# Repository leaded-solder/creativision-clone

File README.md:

# Introduction
TODO

# Current Status

After bodging, version 0.1 of the Derivavision runs a game of _Sonic Invaders_, but a controller interface has not yet been developed. No other cartridges have been tested.

# Thank You
 - [Creativision Datasette Interface](http://www.8bit-homecomputermuseum.at/repair/creativision_datasette_interface/Creativision_datasette_interface.html) for clearing up the mystery of J3
 - Scouter3d for [keyboard and joystick mappings](http://www.madrigaldesign.it/forum/viewtopic.php?t=354)

# Other Libraries
 - [6502-kicad-library](https://github.com/Alarm-Siren/6502-kicad-library): 6502A CPU symbol
 - [CreativisionMegaCartV2](https://github.com/cheshirenoir/CreativisionMegaCartV2) for help with the cartridge edge

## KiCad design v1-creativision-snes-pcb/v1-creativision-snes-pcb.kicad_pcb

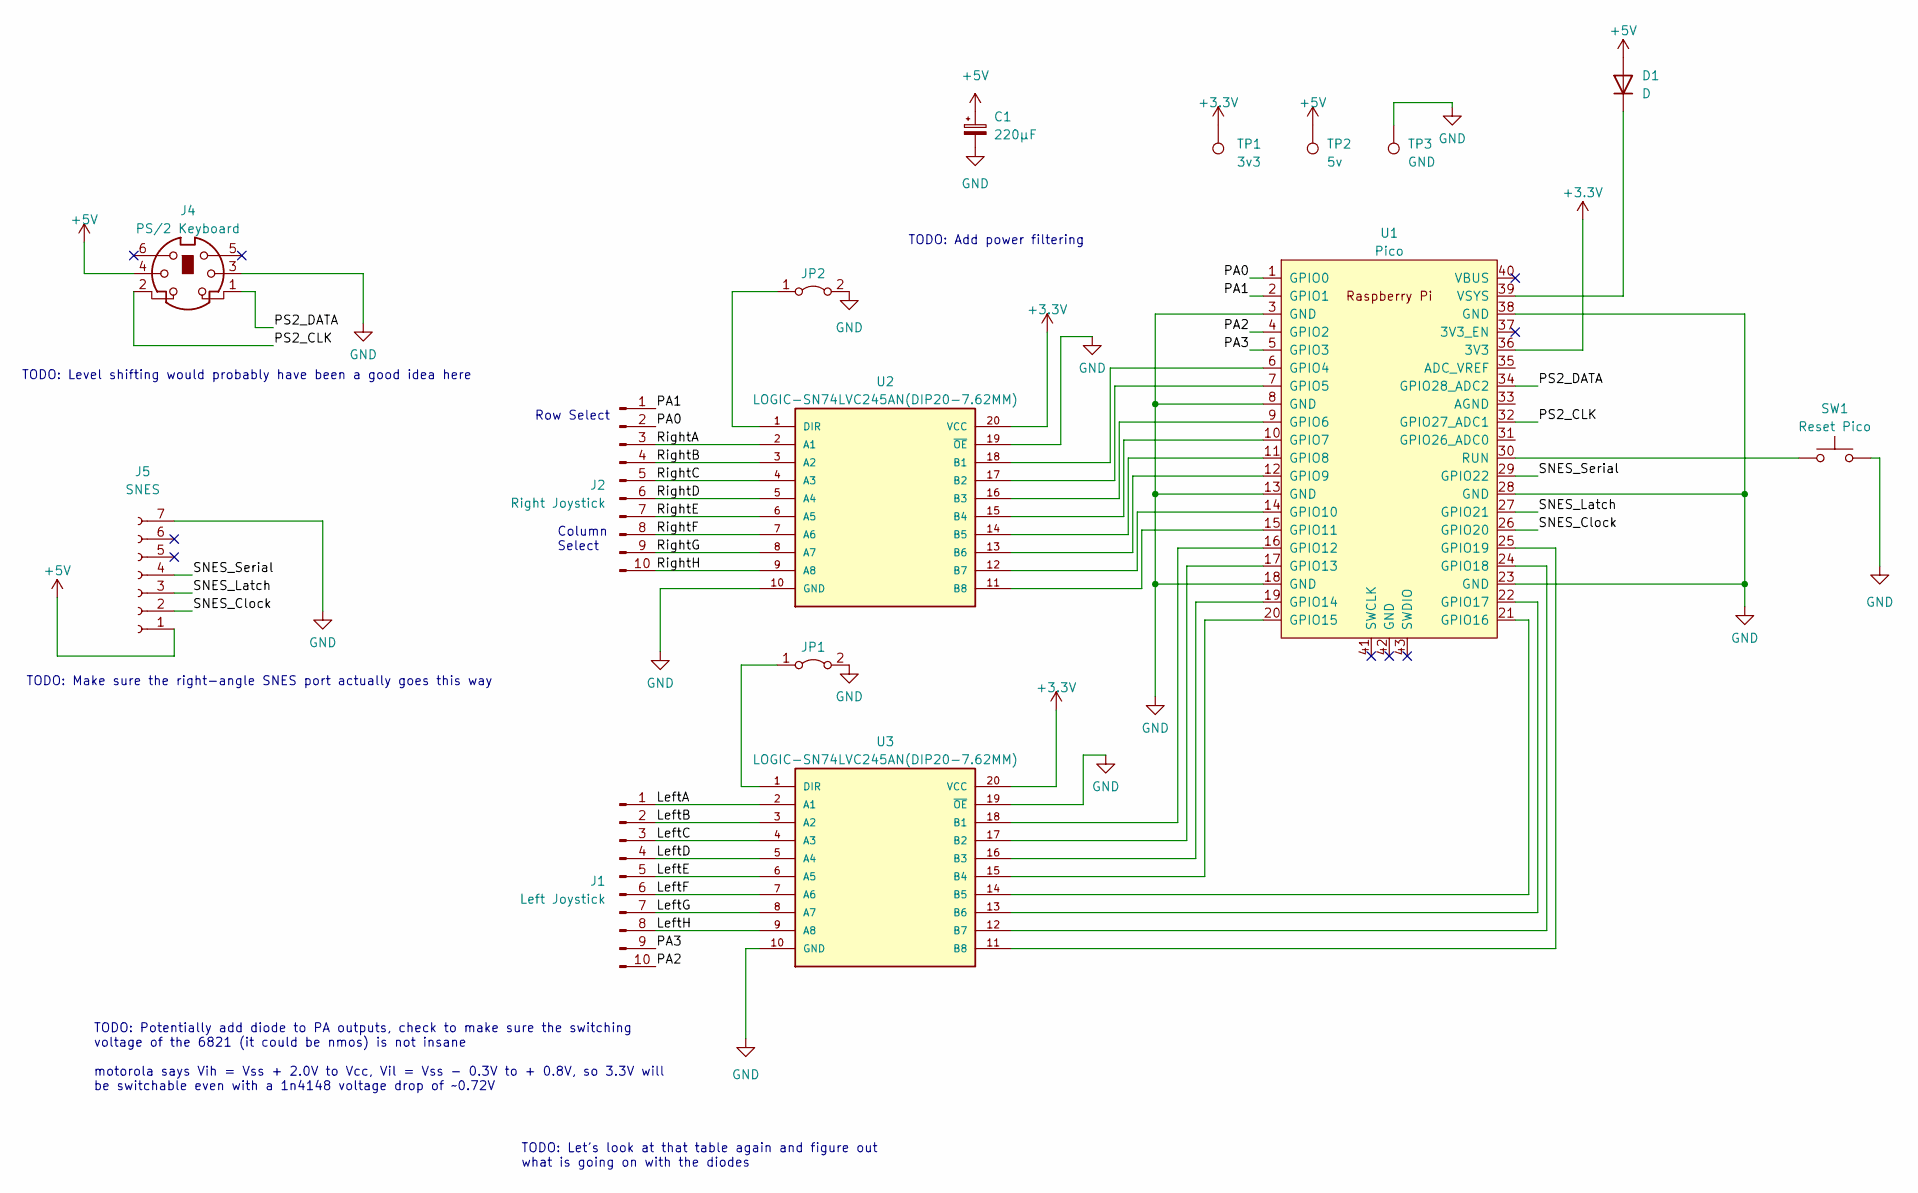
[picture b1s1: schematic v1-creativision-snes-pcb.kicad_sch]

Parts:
C1: 220µF; CP_Radial_D6.3mm_P2.50mm
D1: D; D_DO-15_P10.16mm_Horizontal
J1: Left Joystick; PinHeader_1x10_P2.54mm_Horizontal
J2: Right Joystick; PinHeader_1x10_P2.54mm_Horizontal
J4: PS/2 Keyboard; CUI_MD-60FC
J5: SNES; GAMING_SNES
JP1, JP2: Jumper_2_Bridged; SolderJumper-2_P1.3mm_Bridged2Bar_Pad1.0x1.5mm
SW1: Reset Pico; SW_PUSH_6mm
TP1: 3v3; TestPoint_Loop_D1.80mm_Drill1.0mm_Beaded
TP2: 5v; TestPoint_Loop_D1.80mm_Drill1.0mm_Beaded
TP3: GND; TestPoint_Loop_D1.80mm_Drill1.0mm_Beaded
U1: Pico; RPi_Pico_SMD_TH
U2, U3: LOGIC-SN74LVC245AN(DIP20-7.62MM); DIP-20_W7.62mm_Socket_LongPads; MPN SN74LVC245AN; DigiKey_Part_Number 2156-SN74LVC245AN-ND

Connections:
+3.3V: TP1.1, U1.36 (3V3), U2.20 (VCC), U3.20 (VCC)
+5V: C1.1, D1.2 (A), J4.4, J5.1, TP2.1
/LeftA: J1.1, U3.2 (A1)
/LeftB: J1.2, U3.3 (A2)
/LeftC: J1.3, U3.4 (A3)
/LeftD: J1.4, U3.5 (A4)
/LeftE: J1.5, U3.6 (A5)
/LeftF: J1.6, U3.7 (A6)
/LeftG: J1.7, U3.8 (A7)
/LeftH: J1.8, U3.9 (A8)
/PA0: J2.2, U1.1 (GPIO0)
/PA1: J2.1, U1.2 (GPIO1)
/PA2: J1.10, U1.4 (GPIO2)
/PA3: J1.9, U1.5 (GPIO3)
/PS2_CLK: J4.2, U1.32 (GPIO27_ADC1)
/PS2_DATA: J4.1, U1.34 (GPIO28_ADC2)
/RightA: J2.3, U2.2 (A1)
/RightB: J2.4, U2.3 (A2)
/RightC: J2.5, U2.4 (A3)
/RightD: J2.6, U2.5 (A4)
/RightE: J2.7, U2.6 (A5)
/RightF: J2.8, U2.7 (A6)
/RightG: J2.9, U2.8 (A7)
/RightH: J2.10, U2.9 (A8)
/SNES_Clock: J5.2, U1.26 (GPIO20)
/SNES_Latch: J5.3, U1.27 (GPIO21)
/SNES_Serial: J5.4, U1.29 (GPIO22)
GND: C1.2, J4.3, J5.7, JP1.2 (B), JP2.2 (B), SW1.2, TP3.1, U1.3 (GND), U1.8 (GND), U1.13 (GND), U1.18 (GND), U1.23 (GND), U1.28 (GND), U1.38 (GND), U2.10 (GND), U2.19 (~OE), U3.10 (GND), U3.19 (~OE)
unnamed: D1.1 (K), U1.39 (VSYS)
unnamed: JP1.1 (A), U3.1 (DIR)
unnamed: JP2.1 (A), U2.1 (DIR)
unnamed: U1.6 (GPIO4), U2.18 (B1)
unnamed: U1.7 (GPIO5), U2.17 (B2)
unnamed: U1.9 (GPIO6), U2.16 (B3)
unnamed: U1.10 (GPIO7), U2.15 (B4)
unnamed: U1.11 (GPIO8), U2.14 (B5)
unnamed: U1.12 (GPIO9), U2.13 (B6)
unnamed: U1.14 (GPIO10), U2.12 (B7)
unnamed: U1.15 (GPIO11), U2.11 (B8)
unnamed: U1.16 (GPIO12), U3.18 (B1)
unnamed: U1.17 (GPIO13), U3.17 (B2)
unnamed: U1.19 (GPIO14), U3.16 (B3)
unnamed: U1.20 (GPIO15), U3.15 (B4)
unnamed: U1.21 (GPIO16), U3.14 (B5)
unnamed: U1.22 (GPIO17), U3.13 (B6)
unnamed: U1.24 (GPIO18), U3.12 (B7)
unnamed: U1.25 (GPIO19), U3.11 (B8)
unnamed: SW1.1, U1.30 (RUN)

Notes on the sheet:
TODO: Make sure the right-angle SNES port actually goes this way
Column Select
TODO: Potentially add diode to PA outputs, check to make sure the switching voltage of the 6821 (it could be nmos) is not insane motorola says Vih = Vss + 2.0V to Vcc, Vil = Vss - 0.3V to + 0.8V, so 3.3V will be switchable even with a 1n4148 voltage drop of ~0.72V
TODO: Level shifting would probably have been a good idea here
TODO: Add power filtering
TODO: Let's look at that table again and figure out what is going on with the diodes
Row Select

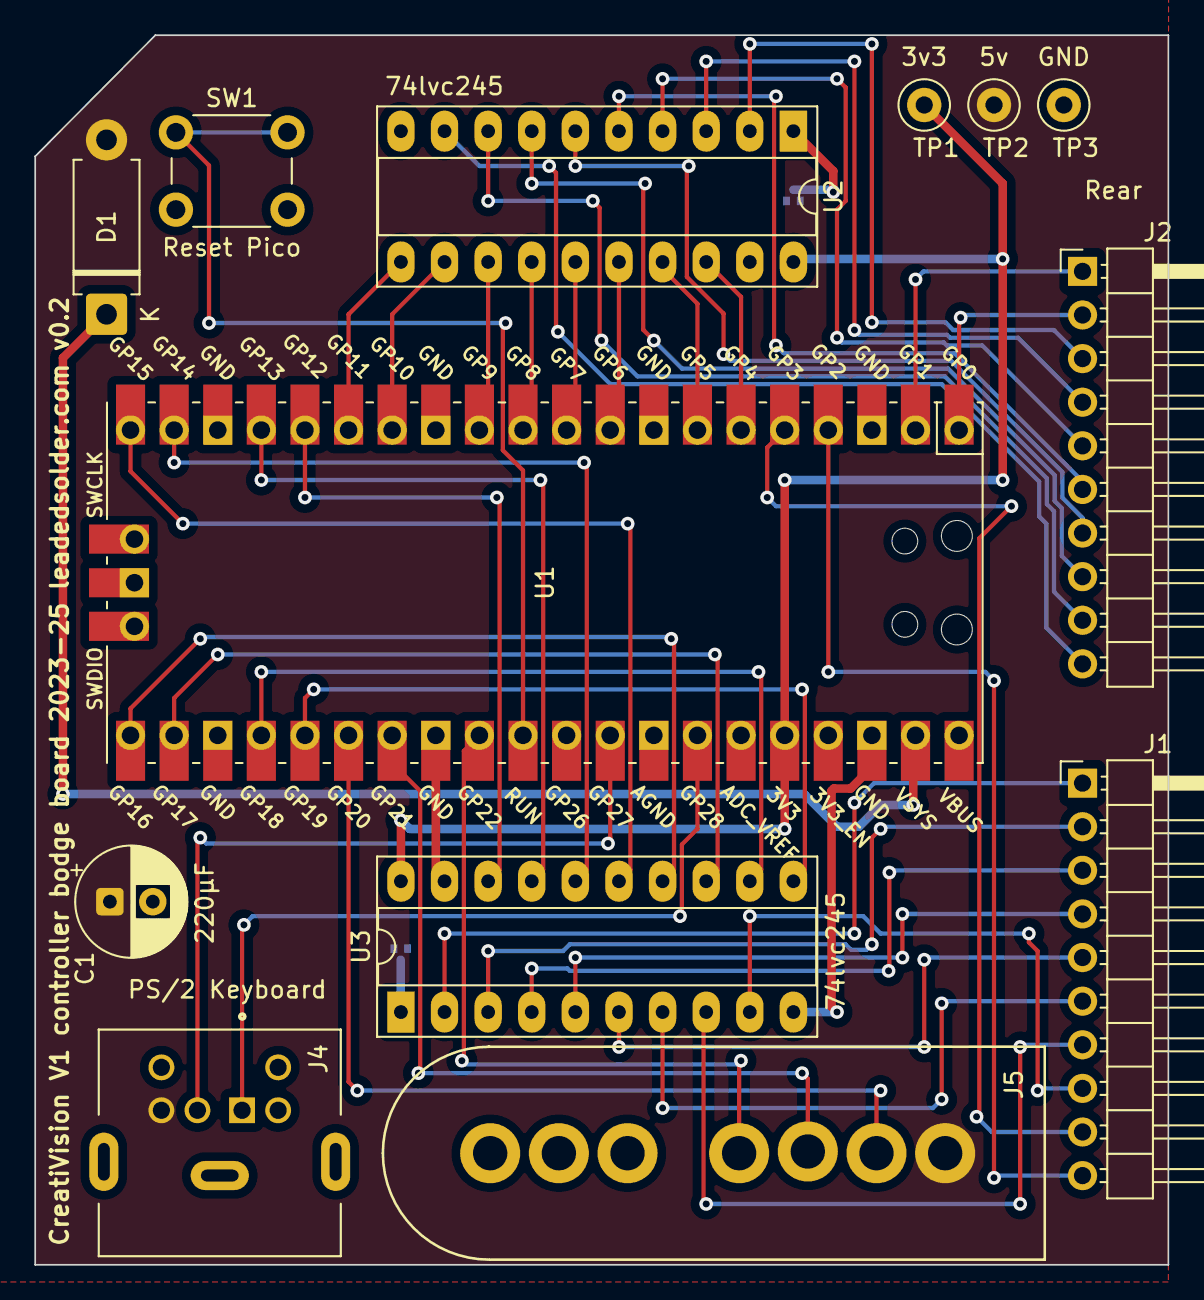
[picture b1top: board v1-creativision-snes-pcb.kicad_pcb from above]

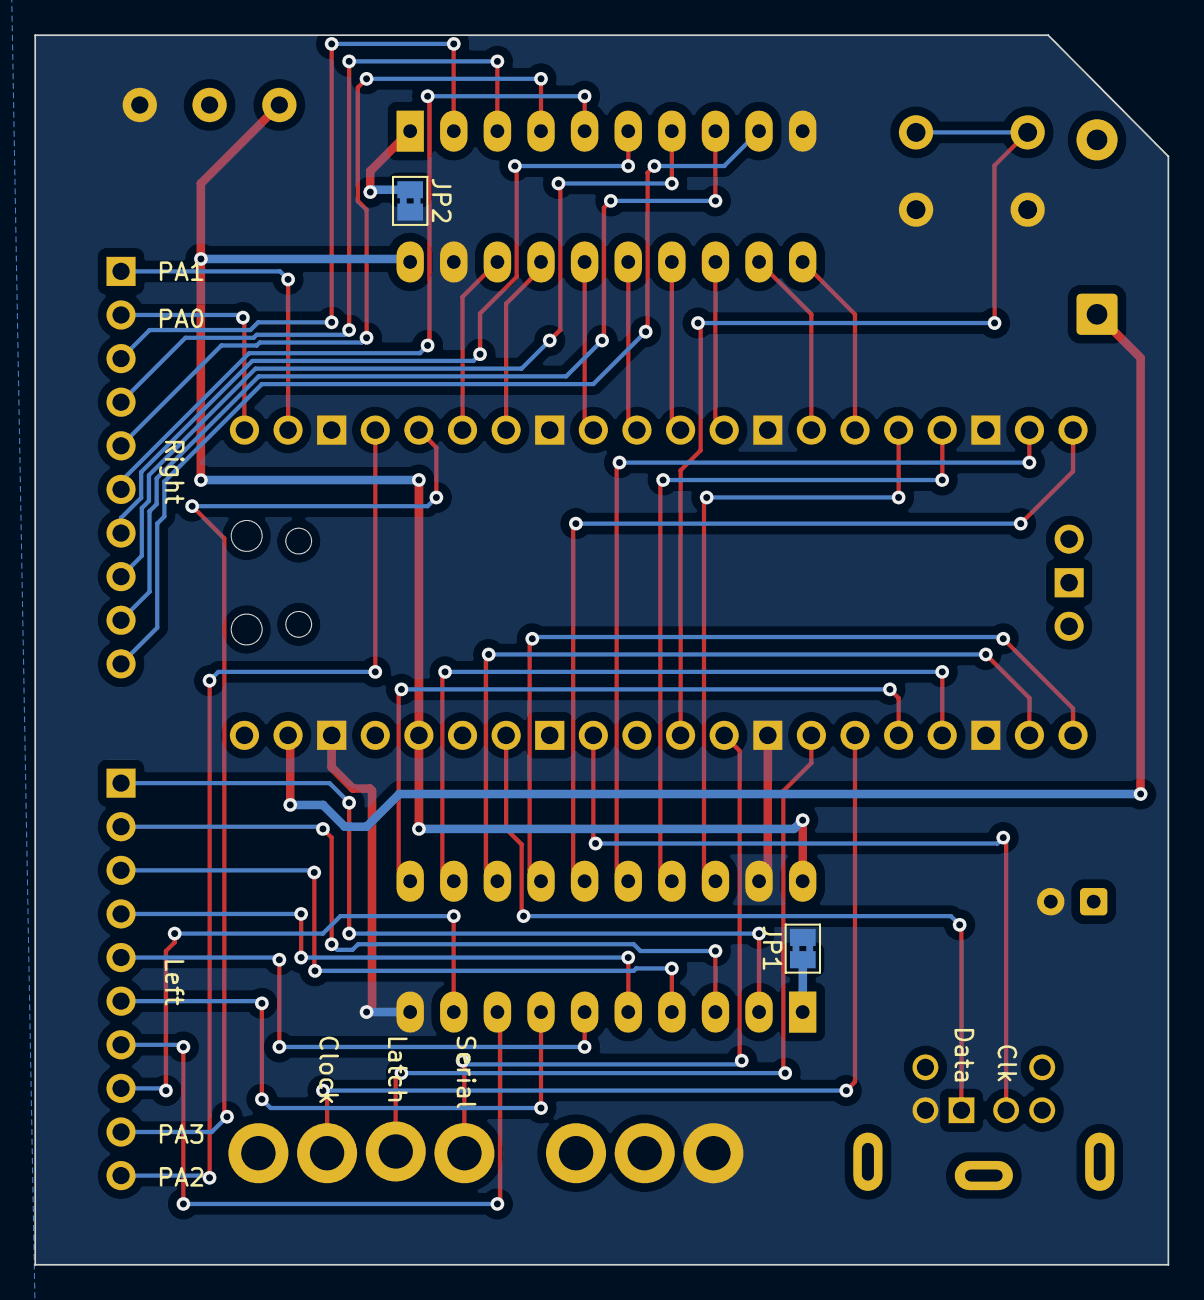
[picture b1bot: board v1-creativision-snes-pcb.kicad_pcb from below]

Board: 2 copper layers, 66.0 x 71.6 mm, 15 parts (2 on the bottom side), 48 nets.

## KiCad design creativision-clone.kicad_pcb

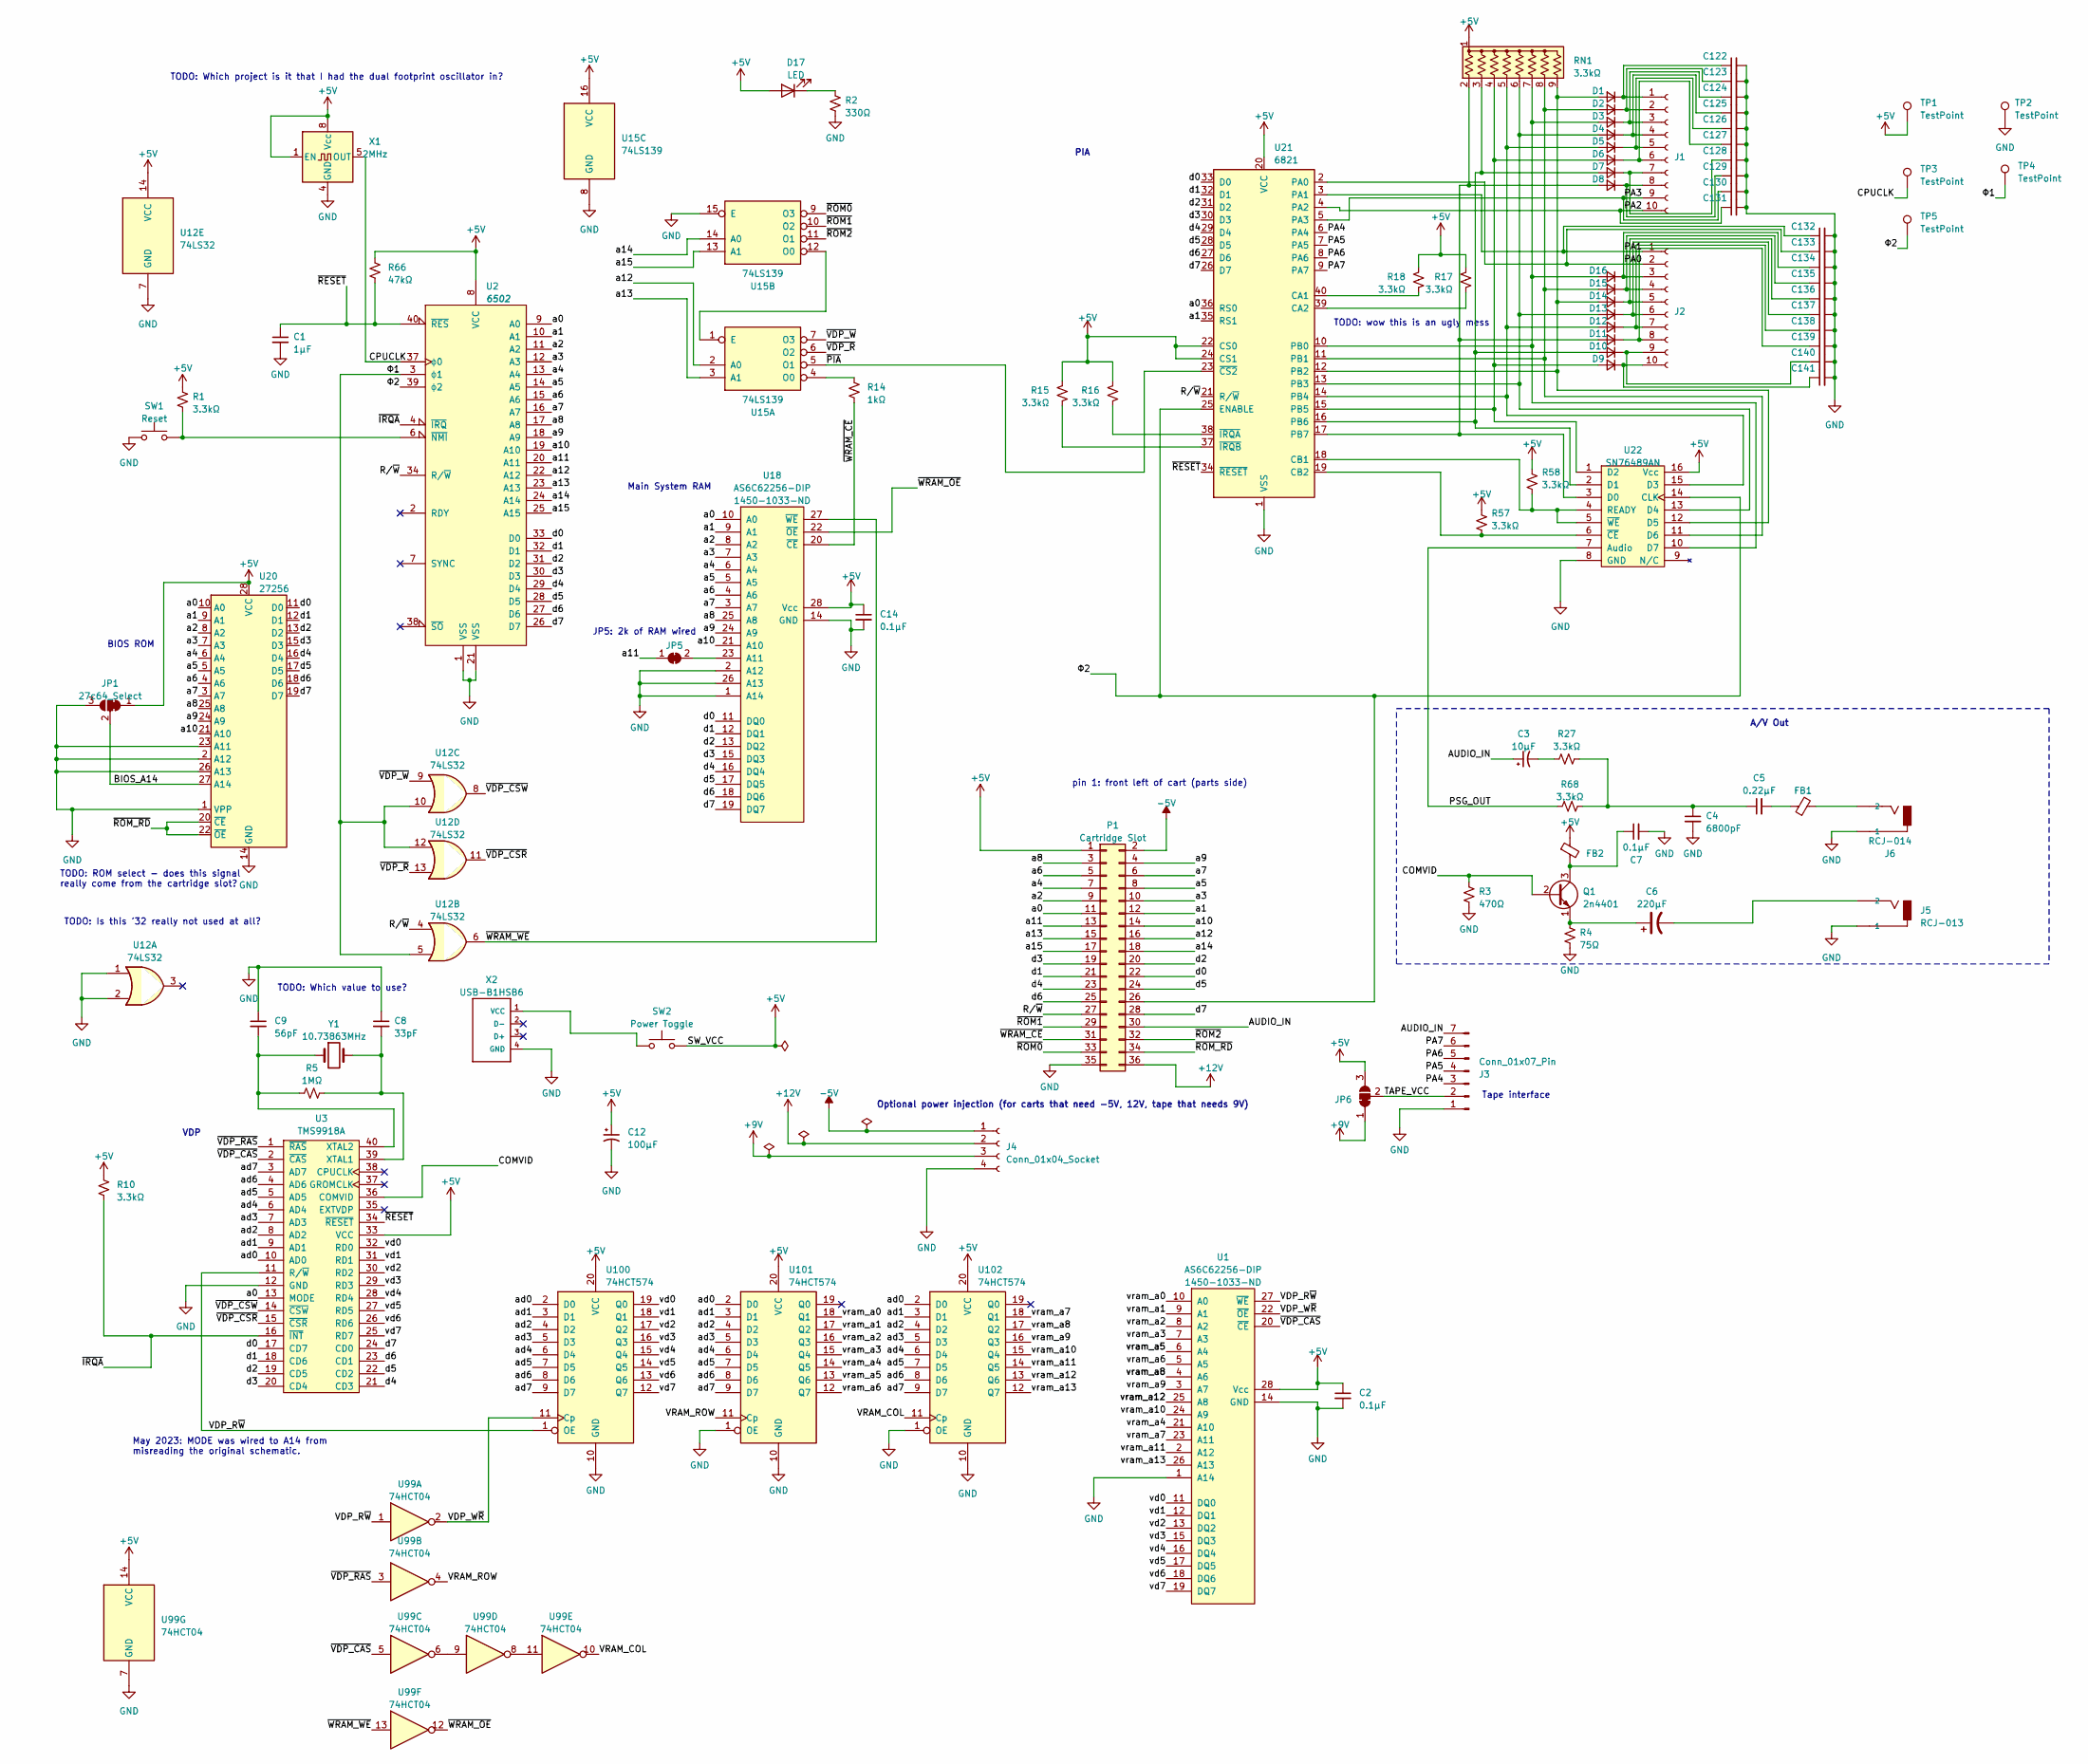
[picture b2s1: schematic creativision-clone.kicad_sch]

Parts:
C1: 1µF; C_Disc_D5.0mm_W2.5mm_P2.50mm
C2, C7, C14: 0.1µF; C_Disc_D5.0mm_W2.5mm_P2.50mm
C3: 10µF; CP_Radial_D5.0mm_P2.50mm
C4: 6800pF; C_Disc_D5.0mm_W2.5mm_P2.50mm
C5: 0.22µF; C_Disc_D5.0mm_W2.5mm_P2.50mm
C6: 220µF; CP_Radial_D6.3mm_P2.50mm
C8: 33pF; C_Disc_D5.0mm_W2.5mm_P2.50mm
C9: 56pF; C_Disc_D5.0mm_W2.5mm_P2.50mm
C12: 100µF; CP_Radial_D6.3mm_P2.50mm
C122, C123, C124, C125, C126, C127, C128, C129, C130, C131, C132, C133, C134, C135, C136, C137, C138, C139, C140, C141: C_Small; C_Disc_D5.0mm_W2.5mm_P2.50mm
D1, D2, D3, D4, D5, D6, D7, D8, D9, D10, D11, D12, D13, D14, D15, D16: D_Small; D_DO-35_SOD27_P7.62mm_Horizontal
D17: LED; LED_D3.0mm
FB1, FB2: FerriteBead_Small; R_Axial_DIN0309_L9.0mm_D3.2mm_P12.70mm_Horizontal; DigiKey 1934-1476-2-ND
J1, J2: Conn_01x10_Socket; PinSocket_1x10_P2.54mm_Vertical
J3: Conn_01x07_Pin; PinHeader_1x07_P2.54mm_Horizontal
J4: Conn_01x04_Socket; PinSocket_1x04_P2.54mm_Vertical
J5: RCJ-013; CUI_RCJ-017; Digi-Key Manufacturer recommendations
J6: RCJ-014; CUI_RCJ-017
JP1: 27c64_Select; SolderJumper-3_P1.3mm_Bridged12_RoundedPad1.0x1.5mm_NumberL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
JP5: SolderJumper_2_Bridged; SolderJumper-2_P1.3mm_Bridged2Bar_RoundedPad1.0x1.5mm
JP6: SolderJumper_3_Bridged12; SolderJumper-3_P1.3mm_Bridged12_RoundedPad1.0x1.5mm_NumberL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
P1: Cartridge Slot; Cartridge_Slot_36p; DigiKey 2-5530843-7-ND
Q1: 2n4401; TO-92_Inline_Wide
R1, R10, R15, R16, R17, R18, R27, R57, R58, R68: 3.3kΩ; R_Axial_DIN0207_L6.3mm_D2.5mm_P10.16mm_Horizontal
R2: 330Ω; R_Axial_DIN0207_L6.3mm_D2.5mm_P10.16mm_Horizontal
R3: 470Ω; R_Axial_DIN0207_L6.3mm_D2.5mm_P10.16mm_Horizontal
R4: 75Ω; R_Axial_DIN0207_L6.3mm_D2.5mm_P10.16mm_Horizontal
R5: 1MΩ; R_Axial_DIN0207_L6.3mm_D2.5mm_P10.16mm_Horizontal
R14: 1kΩ; R_Axial_DIN0207_L6.3mm_D2.5mm_P10.16mm_Horizontal
R66: 47kΩ; R_Axial_DIN0207_L6.3mm_D2.5mm_P10.16mm_Horizontal
RN1: 3.3kΩ; R_Array_SIP9
SW1: Reset; SW_PUSH_6mm
SW2: Power Toggle; PVA1_Switch
TP1, TP2, TP3, TP4, TP5: TestPoint; TestPoint_Loop_D2.50mm_Drill1.0mm
U1, U18: AS6C62256-DIP; DIP-28_W15.24mm_Socket_LongPads; DigiKey 1450-1033-ND
U2: 6502; DIP-40_W15.24mm
U3: TMS9918A; DIP-40_W15.24mm_Socket_LongPads
U12: 74LS32; DIP-14_W7.62mm_Socket_LongPads
U15: 74LS139; DIP-16_W7.62mm_Socket_LongPads
U20: 27256; DIP-28_W15.24mm
U21: 6821; DIP-40_W15.24mm
U22: SN76489AN; DIP-16_W7.62mm_Socket_LongPads
U99: 74HCT04; DIP-14_W7.62mm_Socket_LongPads
U100, U101, U102: 74HCT574; DIP-20_W7.62mm_Socket_LongPads
X1: 2MHz; Oscillator_DIP-8
X2: USB-B1HSB6; OST_USB-B1HSB6; DigiKey ED2983-ND
Y1: 10.73863MHz; Crystal_HC49-4H_Vertical

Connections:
+5V: C2.1, C12.1, C14.1, D17.2 (A), FB2.1, JP1.1 (A), JP6.3 (B), P1.1, R1.1, R10.1, R15.1, R16.1, R17.1, R18.1, R57.1, R58.1, R66.1, RN1.1 (common), SW2.2, TP1.1, U1.28 (Vcc), U2.8 (VCC), U3.33 (VCC), U12.14 (VCC), U15.16 (VCC), U18.28 (Vcc), U20.28 (VCC), U21.20 (VCC), U21.22 (CS0), U21.24 (CS1), U22.16 (Vcc), U99.14 (VCC), U100.20 (VCC), U101.20 (VCC), U102.20 (VCC), X1.1 (EN), X1.8 (Vcc)
+9V: J4.3, JP6.1 (A)
+12V: J4.2, P1.36
-5V: J4.1, P1.2
/AUDIO_IN: C3.1, J3.7, P1.30
/BIOS_A14: JP1.2 (C), U20.27 (A14)
/COMVID: Q1.2 (B), R3.1, U3.36 (COMVID)
/CPUCLK: TP3.1, U2.37 (ϕ0), X1.5 (OUT)
/PA0: C133.1, J2.2, U21.2 (PA0)
/PA1: C132.1, J2.1, U21.3 (PA1)
/PA2: C131.1, J1.10, U21.4 (PA2)
/PA3: C130.1, J1.9, U21.5 (PA3)
/PA4: J3.3, U21.6 (PA4)
/PA5: J3.4, U21.7 (PA5)
/PA6: J3.5, U21.8 (PA6)
/PA7: J3.6, U21.9 (PA7)
/PSG_OUT: R68.1, U22.7 (Audio)
/R/~W: P1.27, U2.34 (R/~W), U12.4, U21.21 (R/~W)
/TAPE_VCC: J3.2, JP6.2 (C)
/VDP_R~W: U1.27 (~WE), U3.11 (R/~W), U99.1, U100.1 (OE)
/VDP_W~R: U1.22 (~OE), U99.2, U100.11 (Cp)
/VRAM_COL: U99.10, U102.11 (Cp)
/VRAM_ROW: U99.4, U101.11 (Cp)
/a0: P1.11, U2.9 (A0), U3.13 (MODE), U18.10 (A0), U20.10 (A0), U21.36 (RS0)
/a1: P1.12, U2.10 (A1), U18.9 (A1), U20.9 (A1), U21.35 (RS1)
/a2: P1.9, U2.11 (A2), U18.8 (A2), U20.8 (A2)
/a3: P1.10, U2.12 (A3), U18.7 (A3), U20.7 (A3)
/a4: P1.7, U2.13 (A4), U18.6 (A4), U20.6 (A4)
/a5: P1.8, U2.14 (A5), U18.5 (A5), U20.5 (A5)
/a6: P1.5, U2.15 (A6), U18.4 (A6), U20.4 (A6)
/a7: P1.6, U2.16 (A7), U18.3 (A7), U20.3 (A7)
/a8: P1.3, U2.17 (A8), U18.25 (A8), U20.25 (A8)
/a9: P1.4, U2.18 (A9), U18.24 (A9), U20.24 (A9)
/a10: P1.14, U2.19 (A10), U18.21 (A10), U20.21 (A10)
/a11: JP5.1 (A), P1.13, U2.20 (A11)
/a12: P1.16, U2.22 (A12), U15.2 (A0)
/a13: P1.15, U2.23 (A13), U15.3 (A1)
/a14: P1.18, U2.24 (A14), U15.14 (A0)
/a15: P1.17, U2.25 (A15), U15.13 (A1)
/ad0: U3.10 (AD0), U100.2 (D0), U101.2 (D0), U102.2 (D0)
/ad1: U3.9 (AD1), U100.3 (D1), U101.3 (D1), U102.3 (D1)
/ad2: U3.8 (AD2), U100.4 (D2), U101.4 (D2), U102.4 (D2)
/ad3: U3.7 (AD3), U100.5 (D3), U101.5 (D3), U102.5 (D3)
/ad4: U3.6 (AD4), U100.6 (D4), U101.6 (D4), U102.6 (D4)
/ad5: U3.5 (AD5), U100.7 (D5), U101.7 (D5), U102.7 (D5)
/ad6: U3.4 (AD6), U100.8 (D6), U101.8 (D6), U102.8 (D6)
/ad7: U3.3 (AD7), U100.9 (D7), U101.9 (D7), U102.9 (D7)
/d0: P1.22, U2.33 (D0), U3.17 (CD7), U18.11 (DQ0), U20.11 (D0), U21.33 (D0)
/d1: P1.21, U2.32 (D1), U3.18 (CD6), U18.12 (DQ1), U20.12 (D1), U21.32 (D1)
/d2: P1.20, U2.31 (D2), U3.19 (CD5), U18.13 (DQ2), U20.13 (D2), U21.31 (D2)
/d3: P1.19, U2.30 (D3), U3.20 (CD4), U18.15 (DQ3), U20.15 (D3), U21.30 (D3)
/d4: P1.23, U2.29 (D4), U3.21 (CD3), U18.16 (DQ4), U20.16 (D4), U21.29 (D4)
/d5: P1.24, U2.28 (D5), U3.22 (CD2), U18.17 (DQ5), U20.17 (D5), U21.28 (D5)
/d6: P1.25, U2.27 (D6), U3.23 (CD1), U18.18 (DQ6), U20.18 (D6), U21.27 (D6)
/d7: P1.28, U2.26 (D7), U3.24 (CD0), U18.19 (DQ7), U20.19 (D7), U21.26 (D7)
/vd0: U1.11 (DQ0), U3.32 (RD0), U100.19 (Q0)
/vd1: U1.12 (DQ1), U3.31 (RD1), U100.18 (Q1)
/vd2: U1.13 (DQ2), U3.30 (RD2), U100.17 (Q2)
/vd3: U1.15 (DQ3), U3.29 (RD3), U100.16 (Q3)
/vd4: U1.16 (DQ4), U3.28 (RD4), U100.15 (Q4)
/vd5: U1.17 (DQ5), U3.27 (RD5), U100.14 (Q5)
/vd6: U1.18 (DQ6), U3.26 (RD6), U100.13 (Q6)
/vd7: U1.19 (DQ7), U3.25 (RD7), U100.12 (Q7)
/vram_a0: U1.10 (A0), U101.18 (Q1)
/vram_a1: U1.9 (A1), U101.17 (Q2)
/vram_a2: U1.8 (A2), U101.16 (Q3)
/vram_a3: U1.7 (A3), U101.15 (Q4)
/vram_a4: U1.21 (A10), U101.14 (Q5)
/vram_a5: U1.6 (A4), U101.13 (Q6)
/vram_a6: U1.5 (A5), U101.12 (Q7)
/vram_a7: U1.23 (A11), U102.18 (Q1)
/vram_a8: U1.4 (A6), U102.17 (Q2)
/vram_a9: U1.3 (A7), U102.16 (Q3)
/vram_a10: U1.24 (A9), U102.15 (Q4)
/vram_a11: U1.2 (A12), U102.14 (Q5)
/vram_a12: U1.25 (A8), U102.13 (Q6)
/vram_a13: U1.26 (A13), U102.12 (Q7)
/~IRQA: R10.2, U2.4 (~IRQ), U3.16 (~INT)
/~PIA: U15.5 (O1), U21.23 (~CS2)
/~RESET: C1.1, R66.2, U2.40 (~RES), U3.34 (~RESET), U21.34 (~RESET)
/~ROM0: P1.33, U15.9 (O3)
/~ROM1: P1.29, U15.10 (O2)
/~ROM2: P1.32, U15.11 (O1)
/~ROM_RD: P1.34, U20.20 (~CE), U20.22 (~OE)
/~VDP_CAS: U1.20 (~CE), U3.2 (~CAS), U99.5
/~VDP_CSR: U3.15 (~CSR), U12.11
/~VDP_CSW: U3.14 (~CSW), U12.8
/~VDP_RAS: U3.1 (~RAS), U99.3
/~VDP_R: U12.13, U15.6 (O2)
/~VDP_W: U12.9, U15.7 (O3)
/~WRAM_CE: P1.31, R14.2, U18.20 (~CE)
/~WRAM_OE: U18.22 (~OE), U99.12
/~WRAM_WE: U12.6, U18.27 (~WE), U99.13
/Φ1: TP4.1, U2.3 (ϕ1), U12.5, U12.10, U12.12
/Φ2: P1.26, TP5.1, U2.39 (ϕ2), U21.25 (ENABLE), U22.14 (CLK)
GND: C1.2, C2.2, C4.2, C7.2, C8.1, C9.1, C12.2, C14.2, C122.2, C123.2, C124.2, C125.2, C126.2, C127.2, C128.2, C129.2, C130.2, C131.2, C132.2, C133.2, C134.2, C135.2, C136.2, C137.2, C138.2, C139.2, C140.2, C141.2, J3.1, J4.4, J5.1A (1), J5.1B (1), J5.1C (1), J6.1A (1), J6.1B (1), J6.1C (1), JP1.3 (B), P1.35, R2.2, R3.2, R4.2, SW1.1, TP2.1, U1.1 (A14), U1.14 (GND), U2.1 (VSS), U2.21 (VSS), U3.12 (GND), U12.1, U12.2, U12.7 (GND), U15.8 (GND), U15.15 (E), U18.1 (A14), U18.2 (A12), U18.14 (GND), U18.26 (A13), U20.1 (VPP), U20.2 (A12), U20.14 (GND), U20.23 (A11), U20.26 (A13), U21.1 (VSS), U22.8 (GND), U99.7 (GND), U100.10 (GND), U101.1 (OE), U101.10 (GND), U102.1 (OE), U102.10 (GND), X1.4 (GND), X2.4 (GND)
unnamed: C3.2, R27.1
unnamed: C4.1, C5.1, R27.2, R68.2
unnamed: C5.2, FB1.1
unnamed: C6.2, J5.2
unnamed: D1.2 (A), D14.2 (A), RN1.9 (R8), U21.12 (PB2), U22.12 (D5)
unnamed: C122.1, D1.1 (K), J1.1
unnamed: C123.1, D2.1 (K), J1.2
unnamed: C124.1, D3.1 (K), J1.3
unnamed: C125.1, D4.1 (K), J1.4
unnamed: C126.1, D5.1 (K), J1.5
unnamed: D6.2 (A), D9.2 (A), RN1.4 (R3), U21.15 (PB5), U22.1 (D2)
unnamed: C127.1, D6.1 (K), J1.6
unnamed: C128.1, D7.1 (K), J1.7
unnamed: C129.1, D8.1 (K), J1.8
unnamed: C141.1, D9.1 (K), J2.10
unnamed: D7.2 (A), D10.2 (A), RN1.3 (R2), U21.16 (PB6), U22.2 (D1)
unnamed: C140.1, D10.1 (K), J2.9
unnamed: D8.2 (A), D11.2 (A), RN1.2 (R1), U21.17 (PB7), U22.3 (D0)
unnamed: C139.1, D11.1 (K), J2.8
unnamed: D5.2 (A), D12.2 (A), RN1.5 (R4), U21.14 (PB4), U22.15 (D3)
unnamed: C138.1, D12.1 (K), J2.7
unnamed: D4.2 (A), D13.2 (A), RN1.6 (R5), U21.13 (PB3), U22.13 (D4)
unnamed: C137.1, D13.1 (K), J2.6
unnamed: C136.1, D14.1 (K), J2.5
unnamed: D2.2 (A), D15.2 (A), RN1.8 (R7), U21.11 (PB1), U22.11 (D6)
unnamed: C135.1, D15.1 (K), J2.4
unnamed: D3.2 (A), D16.2 (A), RN1.7 (R6), U21.10 (PB0), U22.10 (D7)
unnamed: C134.1, D16.1 (K), J2.3
unnamed: D17.1 (K), R2.1
unnamed: FB1.2, J6.2
unnamed: JP5.2 (B), U18.23 (A11)
unnamed: C7.1, FB2.2, Q1.3 (C)
unnamed: C6.1, Q1.1 (E), R4.1
unnamed: R1.2, SW1.2, U2.6 (~NMI)
unnamed: C8.2, R5.1, U3.39 (XTAL1), Y1.2
unnamed: C9.2, R5.2, U3.40 (XTAL2), Y1.1
unnamed: U15.1 (E), U15.12 (O0)
unnamed: R14.1, U15.4 (O0)
unnamed: R18.2, U21.40 (CA1)
unnamed: R17.2, U21.39 (CA2)
unnamed: R58.2, U21.18 (CB1), U22.4 (READY), U22.5 (~WE)
unnamed: R57.2, U21.19 (CB2), U22.6 (~CE)
unnamed: R16.2, U21.38 (~IRQA)
unnamed: R15.2, U21.37 (~IRQB)
unnamed: U99.6, U99.9
unnamed: U99.8, U99.11
unnamed: SW2.1, X2.1 (VCC)

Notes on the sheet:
Main System RAM
BIOS ROM
TODO: Is this '32 really not used at all?
VDP
JP5: 2k of RAM wired
pin 1: front left of cart (parts side)
Optional power injection (for carts that need -5V, 12V, tape that needs 9V)
TODO: wow this is an ugly mess
TODO: Which value to use?
TODO: Which project is it that I had the dual footprint oscillator in?
Tape interface
TODO: ROM select - does this signal really come from the cartridge slot?
PIA
A/V Out
May 2023: MODE was wired to A14 from misreading the original schematic.

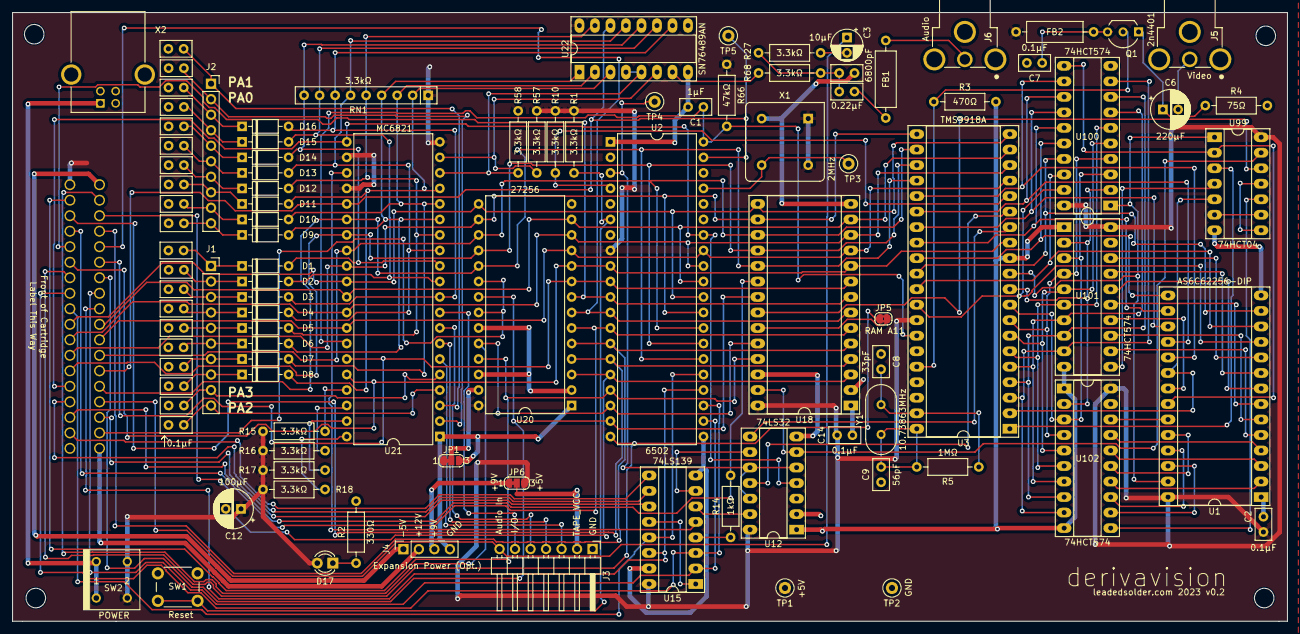
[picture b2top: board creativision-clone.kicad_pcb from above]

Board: 2 copper layers, 208.8 x 99.7 mm, 101 parts (0 on the bottom side), 143 nets.

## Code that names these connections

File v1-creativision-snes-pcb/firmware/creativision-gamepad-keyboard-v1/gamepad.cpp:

#include <stdio.h>
#include "pico/stdlib.h"
#include "hardware/gpio.h"

#include "snespad.h"

#include "ps2read.pio.h"

SnesPad *pad = NULL;

#define PIN_MATRIX_A 0 // "pin 2," right joystick   (~PA0)
#define PIN_MATRIX_B 1 // "pin 1," right joystick   (~PA1)
#define PIN_MATRIX_C 2 // "pin 10," left joystick   (~PA2)
#define PIN_MATRIX_D 3 // "pin 9," left joystick    (~PA3)
// the select lines are mutually exclusive

#define PIN_PS2_DATA 28
#define PIN_PS2_CLOCK 27

#define PIN_LED 25

// Pins GPIO0..GPIO3 inclusive (active low, 0 = selected)
#define INPUT_MATRIX_SELECTS 0x0000f
// Pins GPIO4..GPIO19 inclusive (active low, 0 = pressed)
#define OUTPUT_MATRIX_MASK 0xffff0

unsigned short last_matrix_row; // current matrix row being read

// matrix is A-H, A-H (16 bits)

// GPIO4 -> Right A (pin 3)
// GPIO5 -> Right B (pin 4)
// GPIO6 -> Right C (pin 5)
// GPIO7 -> Right D
// GPIO8 -> Right E
// GPIO9 -> Right F
// GPIO10 -> Right G
// GPIO11 -> Right H

// GPIO12 -> Left A (pin 1)
// GPIO13 -> Left B (pin 2)
// GPIO14 -> Left C (pin 3)
// GPIO15 -> Left D (pin 4)
// GPIO16 -> Left E (pin 5)
// GPIO17 -> Left F (pin 6)
// GPIO18 -> Left G (pin 7)
// GPIO19 -> Left H (pin 8)

// TODO: keyboard/gamepad state
// some kind of keymap structure that is an array to set pins from, where each item is a pointer into the "key state" array
// then we can just drive the mask

// TODO: it probably makes sense to make the keycode a u8 (for row index) and then u16 (for bitmask)

// TODO: something very funky going on with PA0 specifically

/**
 * The entire matrix for all rows (bitmask for RIGHT-LEFT, see above)
 */
unsigned short full_matrix[4];

void trouble() {
    // WE HAVE TROUBLE
    gpio_put(PIN_LED, 1);
}

// Button masks, relative to the "button mask" portion of GPIO (shifted)
#define MASK_RIGHT_A 0x0001
#define MASK_RIGHT_B 0x0002
#define MASK_RIGHT_C 0x0004
#define MASK_RIGHT_D 0x0008
#define MASK_RIGHT_E 0x0010
#define MASK_RIGHT_F 0x0020
#define MASK_RIGHT_G 0x0040
#define MASK_RIGHT_H 0x0080

#define MASK_LEFT_A 0x0100
#define MASK_LEFT_B 0x0200
#define MASK_LEFT_C 0x0400
#define MASK_LEFT_D 0x0800
#define MASK_LEFT_E 0x1000
#define MASK_LEFT_F 0x2000
#define MASK_LEFT_G 0x4000
#define MASK_LEFT_H 0x8000

// also buggy
#define SET_MATRIX2(row, mask) full_matrix[row] &= ~(mask)
// buggy
#define UNSET_MATRIX2(row, mask) full_matrix[row] |= (mask)

void loop(PIO& pio, uint& sm) {
    pad->update();

    SnesButtonState state = pad->get();

    // TODO: Set/reset appropriate matrix pins for controller
    //printf("PA2 matrix = %04X\n", full_matrix[PIN_MATRIX_C]);

    if(state.buttons[SNES_B]) {
        // Fire left (right joystick) PA2 to left-H
        SET_MATRIX2(PIN_MATRIX_C, MASK_LEFT_H);
    }
    else {
        UNSET_MATRIX2(PIN_MATRIX_C, MASK_LEFT_H);
    }

    if(state.buttons[SNES_A]) {
        // Fire Right (right joystick:) PA3 to left-H
        SET_MATRIX2(PIN_MATRIX_D, MASK_LEFT_H);
    }
    else {
        UNSET_MATRIX2(PIN_MATRIX_D, MASK_LEFT_H);
    }

    if(state.buttons[SNES_X]) {
        // Fire right (left joystick:) pin 3 (F) to pin 2 (PA0)
        // This one does not work with the test probe???
        SET_MATRIX2(PIN_MATRIX_A, MASK_RIGHT_F);
    }
    else {
        UNSET_MATRIX2(PIN_MATRIX_A, MASK_RIGHT_F);
    }

    if(state.buttons[SNES_Y]) {
        // Fire left (left joystick:) pin 3 (F) to pin 1 (PA1)
        SET_MATRIX2(PIN_MATRIX_B, MASK_RIGHT_F);
    }
    else {
        UNSET_MATRIX2(PIN_MATRIX_B, MASK_RIGHT_F);
    }

    
    if(state.buttons[SNES_RIGHT]) {
        SET_MATRIX2(PIN_MATRIX_C, MASK_LEFT_A);
    }
    else {
        UNSET_MATRIX2(PIN_MATRIX_C, MASK_LEFT_A);
    }

    if(state.buttons[SNES_LEFT]) {
        SET_MATRIX2(PIN_MATRIX_C, MASK_LEFT_F);
    }
    else {
        UNSET_MATRIX2(PIN_MATRIX_C, MASK_LEFT_F);
    }
    
    /*if(state.buttons[SNES_L]) {
        puts("Left Shoulder is down");
    }
    if(state.buttons[SNES_R]) {
        puts("Right Shoulder is down");
    }
    if(state.buttons[SNES_SELECT]) {
        puts("Select is down");
    }*/

    if(state.buttons[SNES_START]) {
        // Send Z - pin 5 (E) and pin 7 (G) on left controller to PA2
        SET_MATRIX2(PIN_MATRIX_C, MASK_LEFT_A ^ MASK_LEFT_C);
    }
    else {
        UNSET_MATRIX2(PIN_MATRIX_C, MASK_LEFT_A ^ MASK_LEFT_C);
    }

    // TODO: Read PS/2 keyboard as well (ideally interrupt-free, blocking-free) - detect keyup, keydown
    // FIXME: Sometimes the thing is asking for nothing at all (PA0..PA3 all high)

    // TODO: Endianness? Do we need to change the order of the matrix to LEFTRIGHT instead of RIGHTLEFT bytes? i think we have mixed up our left and right controller connectors
    // remember that this is also active low

    // probably the way to do this is some kind of table, so that individual characters
    // will turn on parts of the gpio flags (basically the same table that was made for the PDF)
}

void matrix_changed(uint raw_row, uint32_t events) {
    if(last_matrix_row != raw_row) {        
        last_matrix_row = (unsigned short)raw_row;

        // Change outputs (if needed, this will also pick up key changes during a row)
        gpio_put_masked(OUTPUT_MATRIX_MASK, full_matrix[last_matrix_row] << 4); // HACK
    }
}

int main()
{
    /*
        Pin assignments (TODO: Move this into a header)
        PS/2 clock  - GPIO 27
        PS/2 data   - GPIO 28
        SNES data   - GPIO 22
        SNES latch  - GPIO 21
        SNES clock  - GPIO 20

        Wizz PA0    - GPIO 0 ("pin 2," right joystick)
        Wizz PA1    - GPIO 1 ("pin 1," right joystick)
        Wizz PA2    - GPIO 2 ("pin 10," left joystick)
        Wizz PA3    - GPIO 3 ("pin 9," left joystick)

        Wizz RJoy   - GPIO 4..11 inclusive for A-H
        Wizz LJoy   - GPIO 12..19 inclusive for A-H
    */

    // TODO: Identify RJoy/LJoy matrix inputs changing
    // TODO: Keyboard reading and state

    // TODO: Activate outputs
    // TODO: Set outputs high or low depending on ptr to keyboard state/SNES state
    
    stdio_init_all();

    printf("Hello, world\n");

    // Set directions
    gpio_init_mask(INPUT_MATRIX_SELECTS | OUTPUT_MATRIX_MASK);

    // debug led
    gpio_init(PIN_LED);
    gpio_set_dir(PIN_LED, GPIO_OUT);
    
    gpio_set_dir_in_masked(INPUT_MATRIX_SELECTS);
    gpio_pull_up(PIN_MATRIX_A);
    gpio_pull_up(PIN_MATRIX_B);
    gpio_pull_up(PIN_MATRIX_C);
    gpio_pull_up(PIN_MATRIX_D);
    gpio_set_dir_out_masked(OUTPUT_MATRIX_MASK);

    // Pull everything high. Is this better done with pullups?
    gpio_put_masked(OUTPUT_MATRIX_MASK, OUTPUT_MATRIX_MASK);

    // Clear matrix state
    for(unsigned char i = 0; i < 4; ++i) {
        full_matrix[i] = 0xffff; // it's active low.
    }

    last_matrix_row = 0x00; // force it to re-initialize on first pull

    // Set up interrupts for faster matrix change handling (it's only 60hz, why am I having trouble?)
    gpio_set_irq_enabled_with_callback(PIN_MATRIX_A, GPIO_IRQ_EDGE_FALL, true, &matrix_changed);
    gpio_set_irq_enabled(PIN_MATRIX_B, GPIO_IRQ_EDGE_FALL, true);
    gpio_set_irq_enabled(PIN_MATRIX_C, GPIO_IRQ_EDGE_FALL, true);
    gpio_set_irq_enabled(PIN_MATRIX_D, GPIO_IRQ_EDGE_FALL, true);

    // load PS/2 parsing PIO
    // https://raspico.blogspot.com/2022/05/using-pio-to-interface-ps2-keyboard.html
    PIO pio = pio0;
    uint sm = pio_claim_unused_sm(pio, true);
    uint offset = pio_add_program(pio, &ps2read_program);
    ps2read_program_init(pio, sm, offset, PIN_PS2_CLOCK);
    pio_sm_set_enabled(pio, sm, true);

    // initialize SNES
    pad = new SnesPad();

    while(true) {
        loop(pio, sm);
    }

    return 0;
}

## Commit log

2023-04-11 Empty repo with schematic ref
2023-04-11 ROM wired up
2023-04-11 Work RAM
2023-04-11 Decody.py for 139 config
2023-04-12 6502A wired up
2023-04-12 VDP train, WRAM RD
2023-04-12 keyboard matrix
2023-04-12 Second half of keyboard matrix
2023-04-12 Cartridge filled out except pin 30
2023-04-12 Wire 30
2023-04-13 J3: Cassette interface
2023-04-13 Audio out
2023-04-13 AV out
2023-04-13 TMS9918 Xtal, bypass caps for optional Vs
2023-04-13 Power switch
2023-04-13 Beginning footprint assignment
2023-04-13 Almost complete footprint assignment
2023-04-13 Footprints except cart
2023-04-13 Partial layout
2023-04-14 Enough for one night
2023-04-14 Mounting holes
2023-04-14 Fix backwards tape header
2023-04-14 Ugly cartridge connector
2023-04-14 Make holes smaller on cart slot so traces can fit between
2023-04-14 Data bus and control signals laid out on cart
2023-04-14 Power pour problems
2023-04-14 More plane problems
2023-04-14 Placed and routed, 0 DRC
2023-04-15 Move caps for guaranteed x-clearance
2023-04-15 Hide Kathode designators
2023-04-15 Label power switches
2023-04-15 Add silk for a resistor
2023-04-28 Ignore build products
2023-05-24 Add jumper to default 27c64 pin 27 to high
2023-05-25 Flip polarity of series filter cap
2023-05-25 Remove REF marks for mounting holes
2023-05-28 Fix MODE pin on TMS9918
2023-05-28 Works
2023-05-28 Create LICENSE
2023-09-01 SNES PCB breakout begins
2023-09-02 Swap keyboard and SFC for strain relief
2023-09-03 Wired up connectors to RPi Pico, still TBD on how to do 'shorting'
2023-09-03 Power pico, add reset button for pico
2023-09-04 Use 74lvc245 instead of voltage divider
2023-09-11 PCB all joined up with the lvc strategy
2023-09-11 V1 released to Jlcpcb
2024-01-26 Generated files
2024-01-26 Gamepad firmware stub
2024-01-26 Basics of SNES reading (untested)
2024-02-09 Better notes
2024-02-09 Readme to warn people it's a WIP
2024-02-09 Output over USB, but shifting is not working
2024-02-09 Something wrong with clockout
2024-02-09 Something is not working with the GPIOs
2024-02-09 Still not working
2024-02-09 Backwards clock
2024-02-09 Fighting it
2024-02-09 Working PoC for reading SNES
2024-03-02 key mappings reference from Scouter3D http://www.madrigaldesign.it/forum/viewtopic.php?t=354
2024-08-09 Fix picosdk finding
2024-08-09 Idle fiddling
2024-08-09 notes for later
2024-10-25 Detecting matrix change, maybe
2024-10-29 Internal notes
2024-12-26 Update Pico SDK
2024-12-26 Notes for next time
2024-12-26 Call into the PIO
2024-12-26 Pass PIO to somewhere to use it
2025-09-13 maybe smarter masking system
2025-09-13 Active low bungle
2025-09-13 Saving myself time by reading directions
2025-09-14 Try to set initial in/out state, maybe I'm being clever
2025-09-14 Clumsy attempt at getting Fire B to work
2025-09-15 Add diode to prevent backpowering when uploading firmware
2025-09-25 Trying to add extra debug buttons
2025-09-25 KiCad update, label PAx pins on headers
2025-10-03 Still not working but bit math is a little better
2025-10-03 Matrix read was bonked
2025-10-04 Get rid of spurious loop
2025-10-04 Flash command
2025-10-04 I forgot gpio_init AGAIN
2025-10-04 Replace stupid mistake
2025-10-04 Matrix decoding still not working properly
2025-10-04 Sometimes no scan is done at all
2025-10-04 It's PA3
2025-10-05 Fix DIR pin error
2025-10-05 Matrix scanning is not working how I expected
2025-10-05 PA3..0 are backward from what I expected
2025-10-05 Don't get off the bus when they're not asking
2025-10-05 It's working, leave it for today
2025-10-05 LEAVE IT
2025-10-07 trying to figure out player 1 firing
2025-10-07 All four fire buttons work now
2025-10-07 Fast scan reintroduced
2025-10-07 The scanning is still goofed
2025-10-07 Interrupt-driven matrix scanning, so much better
